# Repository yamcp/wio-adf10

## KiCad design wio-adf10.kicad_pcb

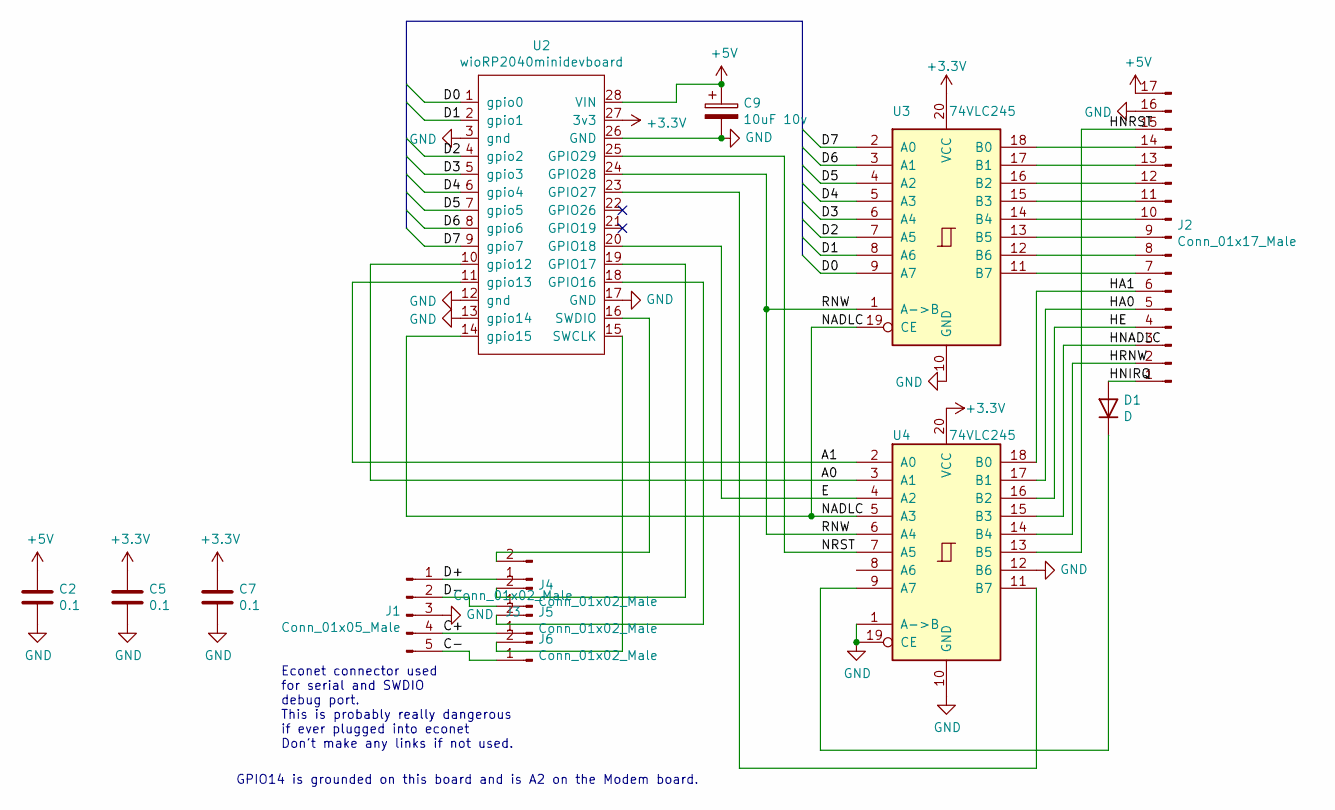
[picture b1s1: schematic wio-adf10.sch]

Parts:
C2, C5, C7: 0.1; C_Rect_L7.0mm_W2.5mm_P5.00mm
C9: 10uF 10v; CP_Radial_D5.0mm_P2.50mm
D1: D; D_A-405_P7.62mm_Horizontal
J1: Conn_01x05_Male; PinHeader_1x05_P2.54mm_Vertical
J2: Conn_01x17_Male; PinHeader_1x17_P2.54mm_Vertical
J3, J4, J5, J6: Conn_01x02_Male; PinHeader_2x01_P2.54mm_Vertical
U2: wioRP2040minidevboard; Wio=RP2040-mini-dev-board
U3, U4: 74VLC245; DIP-20_W7.62mm

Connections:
+3V3: C5.1, C7.1, U2.27 (3v3), U3.20 (VCC), U4.20 (VCC)
+5V: C2.1, C9.1, J2.17, U2.28 (VIN)
/A0: U2.10 (gpio12), U4.3 (A1)
/A1: U2.11 (gpio13), U4.2 (A0)
/C+: J1.4, J5.1
/C-: J1.5, J6.1
/D0: U2.1 (gpio0), U3.9 (A7)
/D1: U2.2 (gpio1), U3.8 (A6)
/D2: U2.4 (gpio2), U3.7 (A5)
/D3: U2.5 (gpio3), U3.6 (A4)
/D4: U2.6 (gpio4), U3.5 (A3)
/D5: U2.7 (gpio5), U3.4 (A2)
/D6: U2.8 (gpio6), U3.3 (A1)
/D7: U2.9 (gpio7), U3.2 (A0)
/D+: J1.1, J3.1
/D-: J1.2, J4.1
/E: U2.20 (GPIO18), U4.4 (A2)
/HA0: J2.5, U4.17 (B1)
/HA1: J2.6, U4.18 (B0)
/HE: J2.4, U4.16 (B2)
/HNADLC: J2.3, U4.15 (B3)
/HNIRQ: D1.2 (A), J2.1
/HNRST: J2.15, U4.13 (B5)
/HRNW: J2.2, U4.14 (B4)
/NADLC: U2.14 (gpio15), U3.19 (CE), U4.5 (A3)
/NRST: U2.25 (GPIO29), U4.7 (A5)
/RNW: U2.24 (GPIO28), U3.1 (A->B), U4.6 (A4)
GND: C2.2, C5.2, C7.2, C9.2, J1.3, J2.16, U2.3 (gnd), U2.12 (gnd), U2.13 (gpio14), U2.17 (GND), U2.26 (GND), U3.10 (GND), U4.1 (A->B), U4.10 (GND), U4.12 (B6), U4.19 (CE)
unnamed: D1.1 (K), U4.9 (A7)
unnamed: J2.7, U3.11 (B7)
unnamed: J2.8, U3.12 (B6)
unnamed: J2.9, U3.13 (B5)
unnamed: J2.10, U3.14 (B4)
unnamed: J2.11, U3.15 (B3)
unnamed: J2.12, U3.16 (B2)
unnamed: J2.13, U3.17 (B1)
unnamed: J2.14, U3.18 (B0)
unnamed: J3.2, U2.16 (SWDIO)
unnamed: J4.2, U2.19 (GPIO17)
unnamed: J5.2, U2.18 (GPIO16)
unnamed: J6.2, U2.15 (SWCLK)
unnamed: U2.23 (GPIO27), U4.11 (B7)

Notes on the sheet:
Econet connector used for serial and SWDIO debug port. This is probably really dangerous if ever plugged into econet Don't make any links if not used.
GPIO14 is grounded on this board and is A2 on the Modem board.

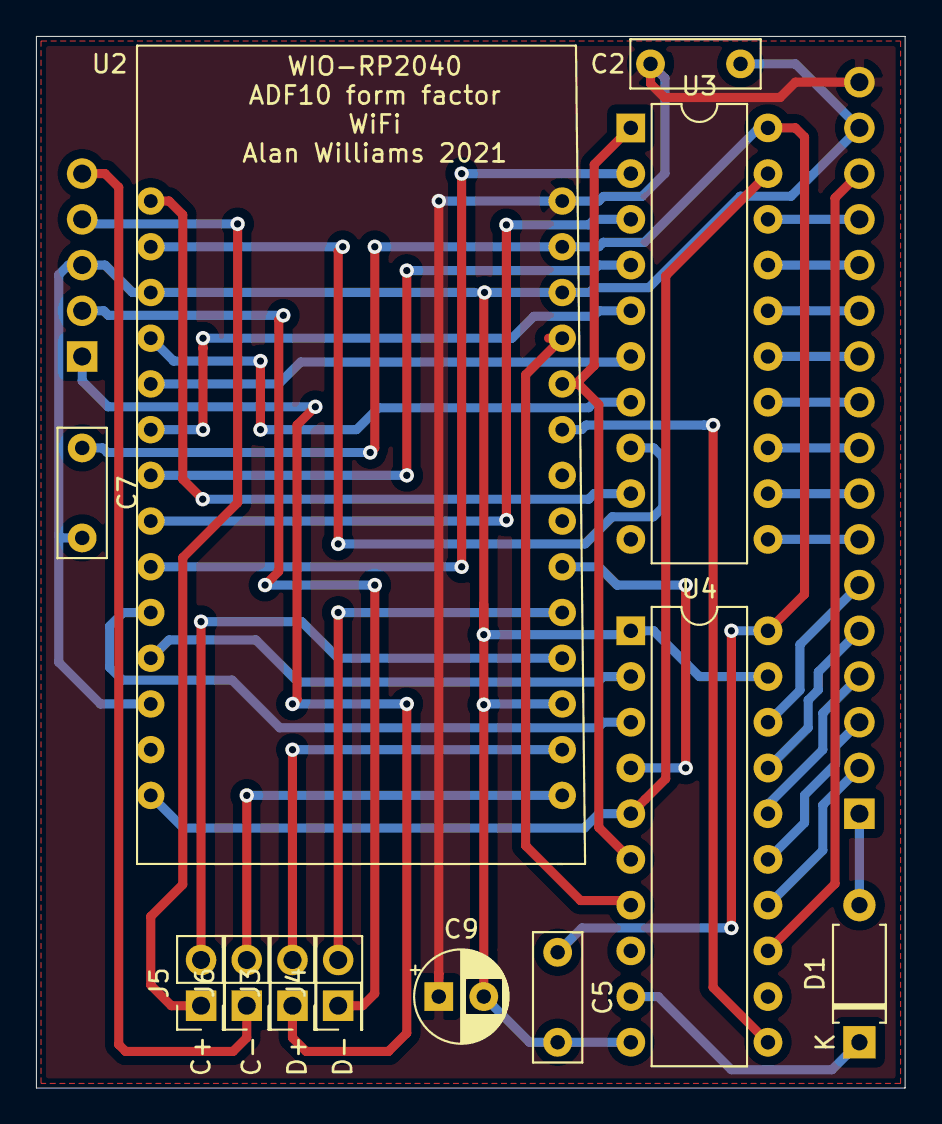
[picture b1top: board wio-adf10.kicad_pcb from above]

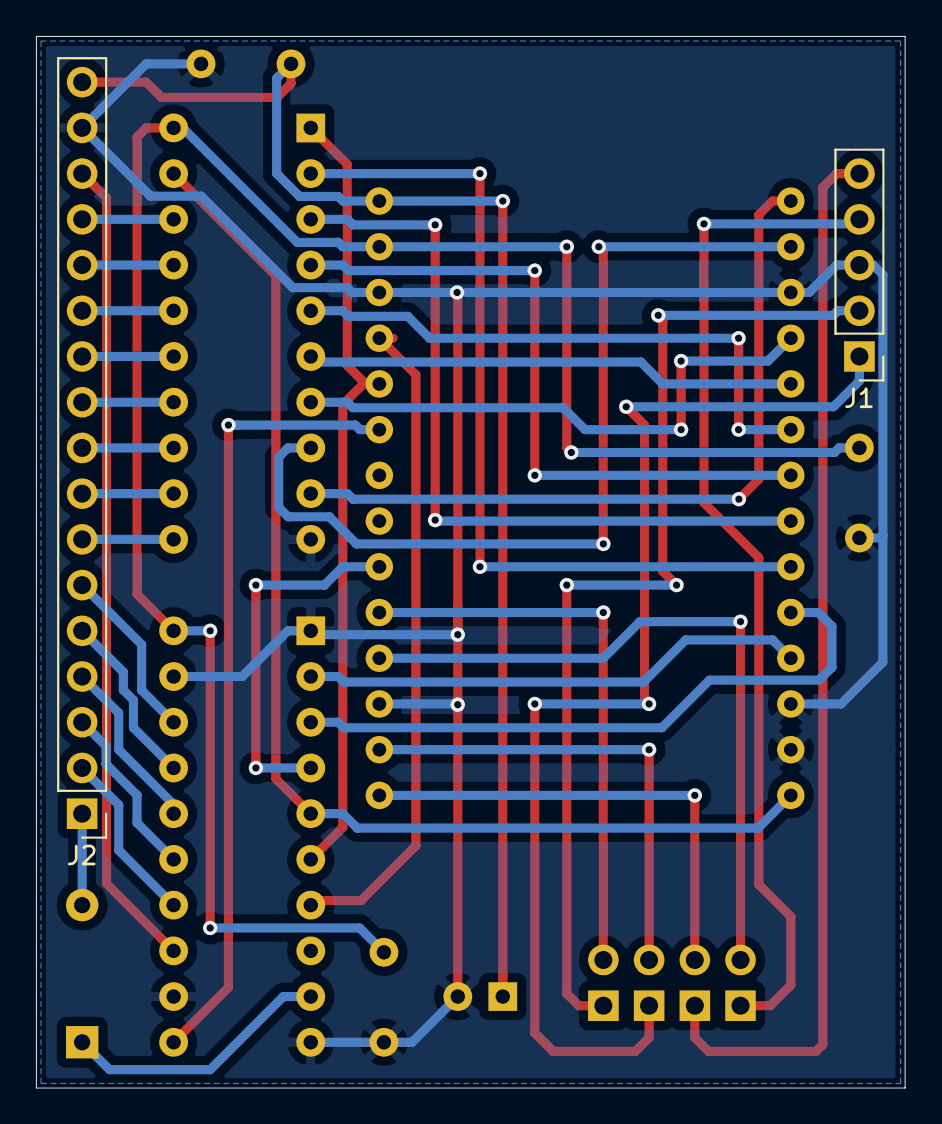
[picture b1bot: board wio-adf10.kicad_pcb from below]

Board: 2 copper layers, 48.3 x 58.4 mm, 14 parts (2 on the bottom side), 42 nets.
